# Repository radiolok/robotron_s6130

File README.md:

# Robotron S6130 и «Элема»: прошивки, схемы, документация

Реверс-инжиниринг и восстановление электронных пишущих машинок серии
**Robotron S6100** (ГДР, 1986–1989) и их советского аналога **«Элема» (ПЭЛК-3110)**.

| Машинка | Процессор | Статус | Документация |
|---|---|---|---|
| **Robotron S6130** | U880 (клон Z80), 2,46 МГц | ✅ **Работает.** Новая материнская плата, разблокирован RS-232 | [s6130/](s6130/README.md) |
| **«Элема» ПЭЛК-3110** | КР580ВМ80А (клон i8080) | 🛠 **Заготовка.** Прошивка снята, схема оцифрована, карта периферии сверена со схемой | [elema/](elema/README.md) |

История оживления «Роботрона»: статья на Хабре
[«Robotron S6130 — Восставший из мертвых»](https://habr.com/ru/companies/yadro/articles/886254/).

## Структура репозитория

```
s6130/            Robotron S6130
  README.md         обзор, журнал оживления, патчи, подключение к ПК
  fw/               дампы ПЗУ, листинг и база IDA, описание прошивки (README.md)
  hw/               описание железа (README.md), документация производителя (doc/),
                    схемы KiCad/DipTrace/draw.io (sch/), иллюстрации (img/)
elema/            «Элема» ПЭЛК-3110
  README.md         обзор и план оживления
  fw/               дампы ПЗУ, листинг i8080, описание прошивки (README.md)
  hw/               расшифровка схемы (README.md), склеенные листы, сканы (scans/),
                    таблицы разъёмов (netlist/)
tools/            общие скрипты
```

| Документ | Что внутри |
|---|---|
| [s6130/README.md](s6130/README.md) | Robotron S6130: обзор, опись файлов, журнал оживления, патчи прошивки, RS-232, инструментарий |
| [s6130/hw/README.md](s6130/hw/README.md) | S6130, железо: карта памяти, порты, прерывания, клавиатура, индикатор, двигатели, RS-232 и DIP-переключатели |
| [s6130/fw/README.md](s6130/fw/README.md) | S6130, **структура прошивки**: загрузка, главный цикл, прерывания, подсистемы, таблицы ПЗУ, переменные ОЗУ |
| [elema/README.md](elema/README.md) | «Элема»: обзор и план оживления |
| [elema/hw/README.md](elema/hw/README.md) | «Элема», железо: расшифровка принципиальной схемы (платы, микросхемы, разъёмы, дешифрация) |
| [elema/fw/README.md](elema/fw/README.md) | «Элема», **структура прошивки**: карта памяти и портов, прерывания ВН59, схема загрузки |

## Инструменты (`tools/`)

| Скрипт | Назначение |
|---|---|
| `z80_trace.py` | Превращает вывод Z80-декодера PulseView/sigrok в читаемую трассу (`.out`) и в Trace Events JSON для [Perfetto UI](https://ui.perfetto.dev) (флейм-чарт вызовов и обращений к портам) |
| `s6130_symbol.py` | Рисует таблицу символов из ПЗУ знакогенератора индикатора S6130 |
| `s6130_mem.py` | Описание карты памяти S6130 |
| `stitch_scans.py` | Склейка фрагментов скана одного листа (SIFT + аффинные преобразования; поворот и масштаб фрагментов любые). Нужен `opencv-python` |

```sh
# Трасса: export.txt — вывод декодера Z80 из PulseView, names.txt — экспорт имён функций из IDA
python3 tools/z80_trace.py -f export.txt -a names.txt              # S6130
python3 tools/z80_trace.py -f export.txt -a names.txt -m elema     # «Элема» (карта портов ПЭЛК)
# → export.txt.out (трасса) и export.txt.json (открыть в https://ui.perfetto.dev)

# Таблица символов индикатора
python3 tools/s6130_symbol.py -f s6130/fw/symbol_rom.bin -o charset.png

# Склейка листа схемы из фрагментов (--ref — номер фрагмента, задающего ориентацию)
python3 tools/stitch_scans.py -o sheet.png --ref 2 part1.jpg part2.jpg part3.jpg
```

Как устроен процесс отладки, описано в [s6130/README.md](s6130/README.md#инструментарий).

## Ссылки

- Статья: [Robotron S6130 — Восставший из мертвых](https://habr.com/ru/companies/yadro/articles/886254/) (Хабр, блог YADRO, 2025)
- [sigrok / PulseView](https://sigrok.org) — логический анализатор и декодер Z80
- [Perfetto UI](https://ui.perfetto.dev) — просмотр трасс

## Лицензия

[BSD 2-Clause](LICENSE). Документация производителя (`s6130/hw/doc/`, сканы в `elema/hw/`)
принадлежит правообладателям и приведена в справочных целях.

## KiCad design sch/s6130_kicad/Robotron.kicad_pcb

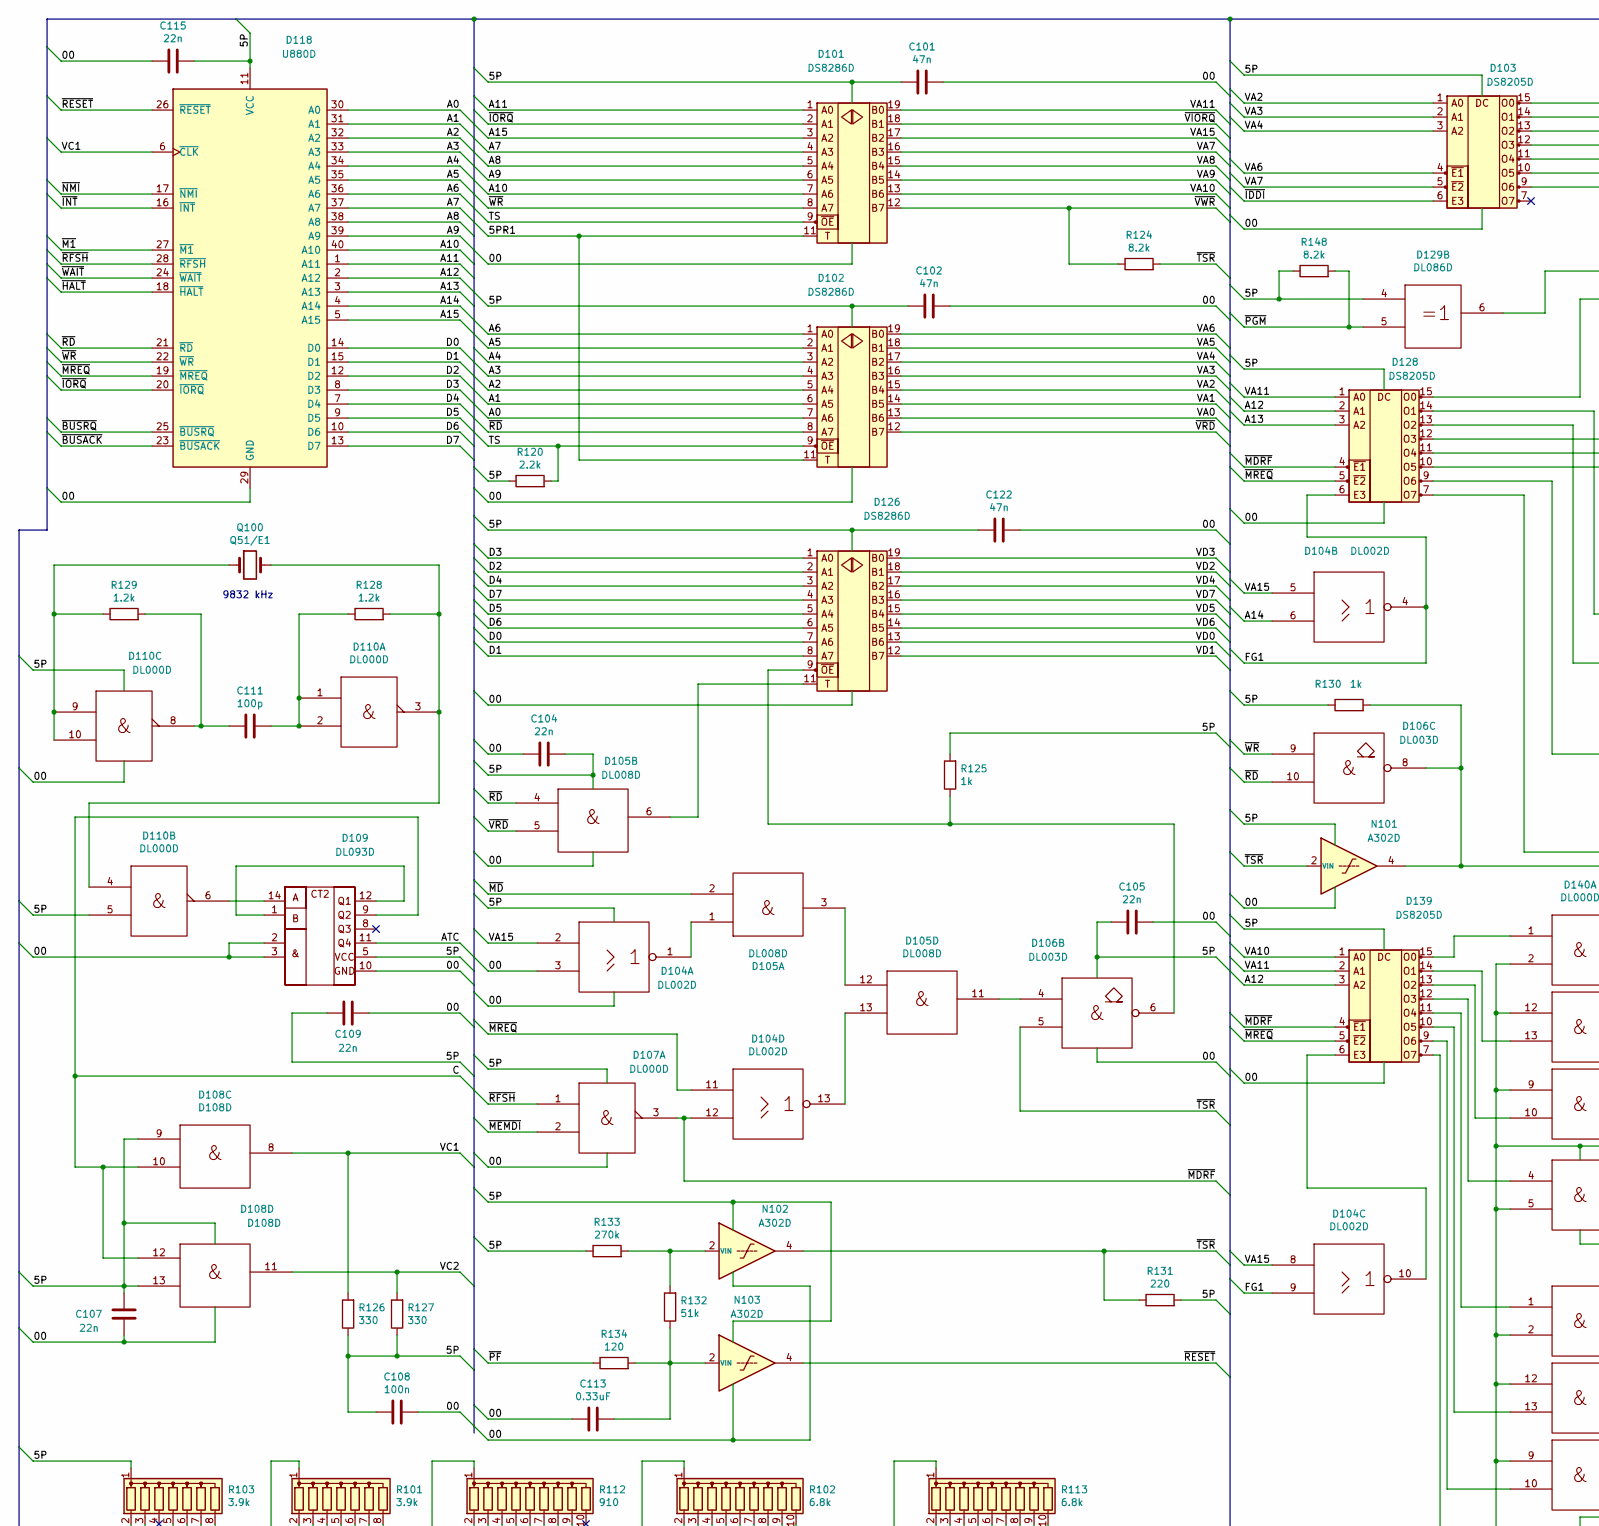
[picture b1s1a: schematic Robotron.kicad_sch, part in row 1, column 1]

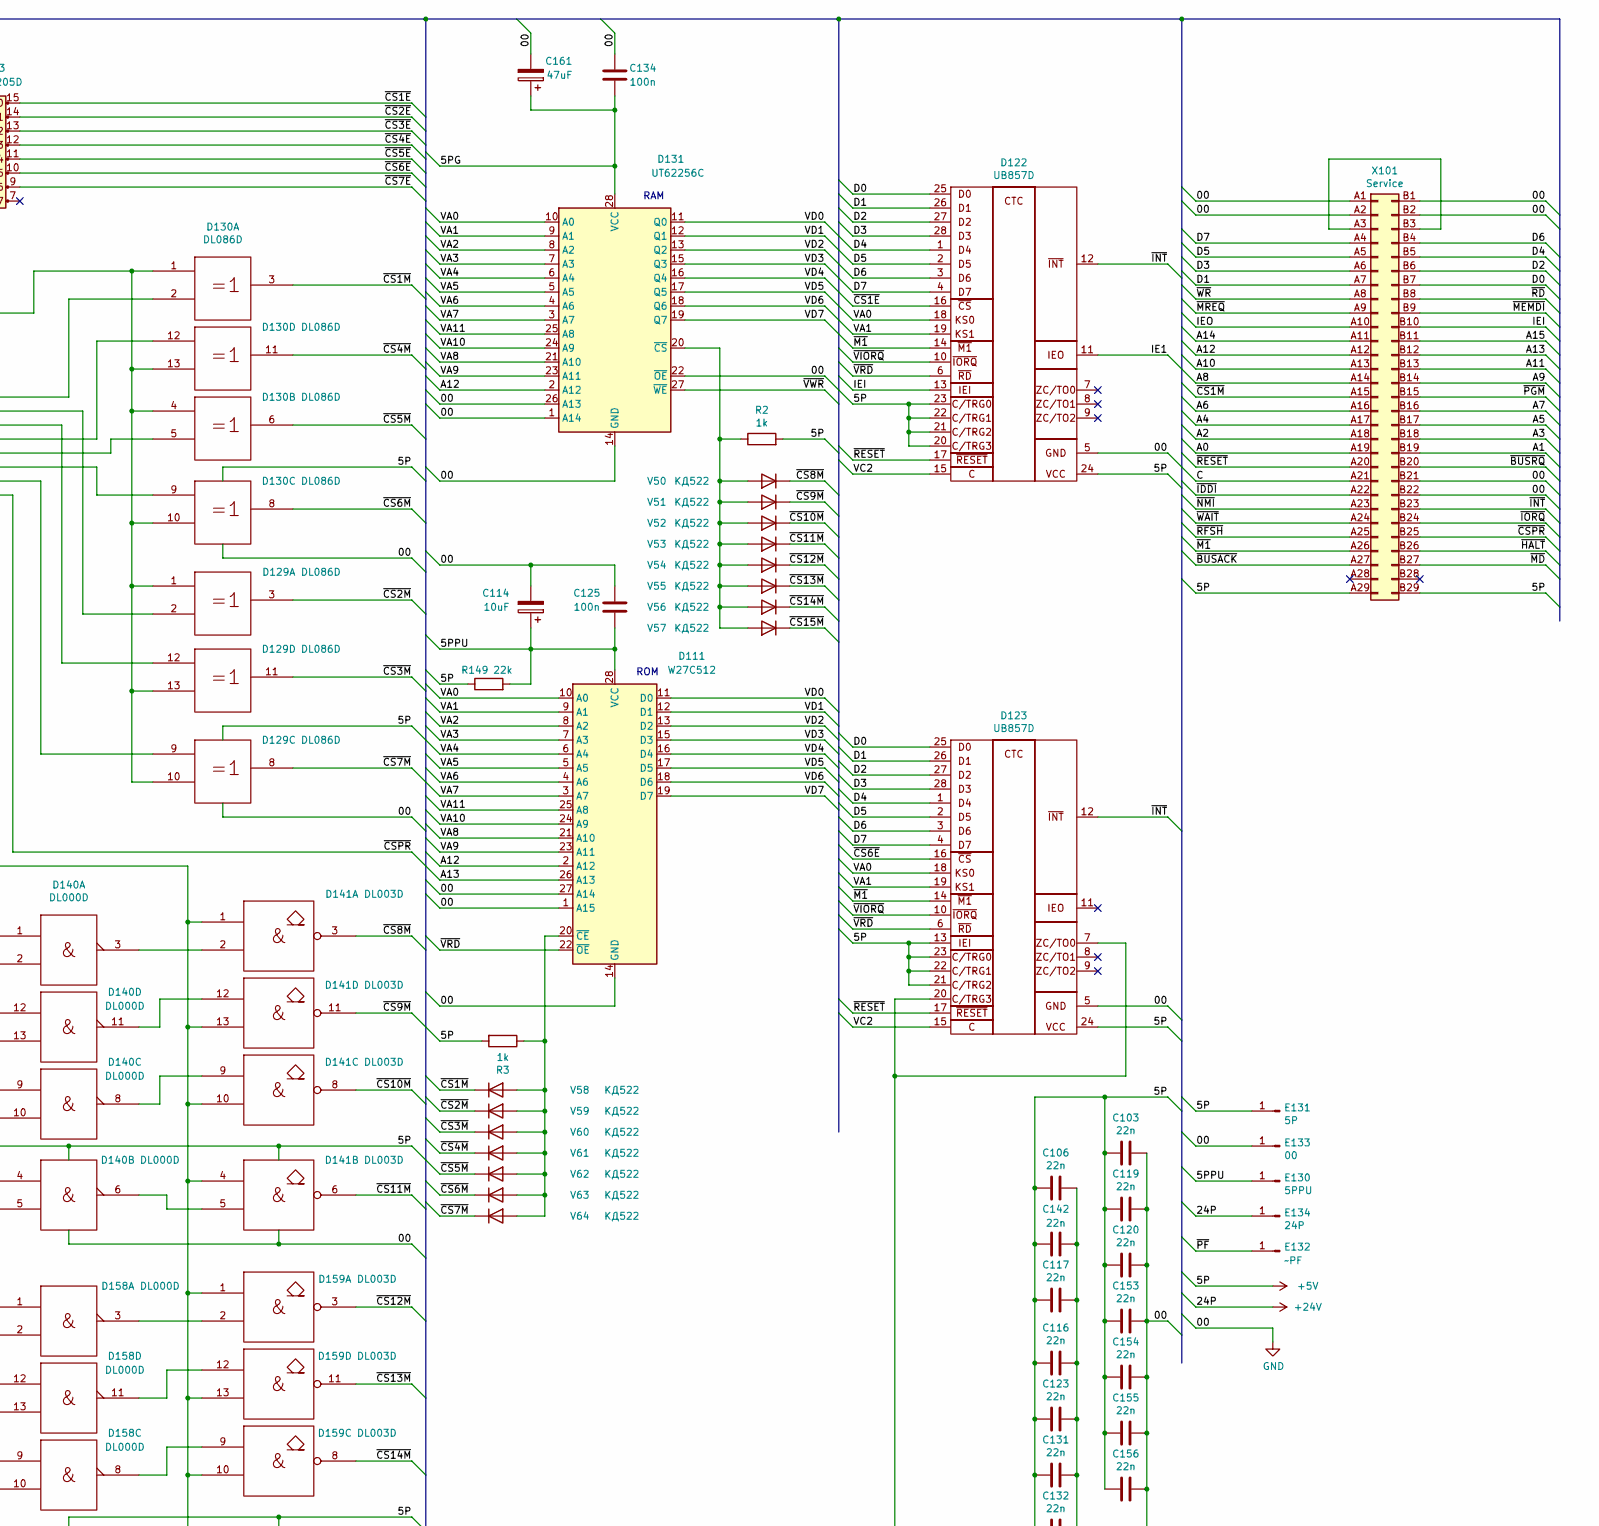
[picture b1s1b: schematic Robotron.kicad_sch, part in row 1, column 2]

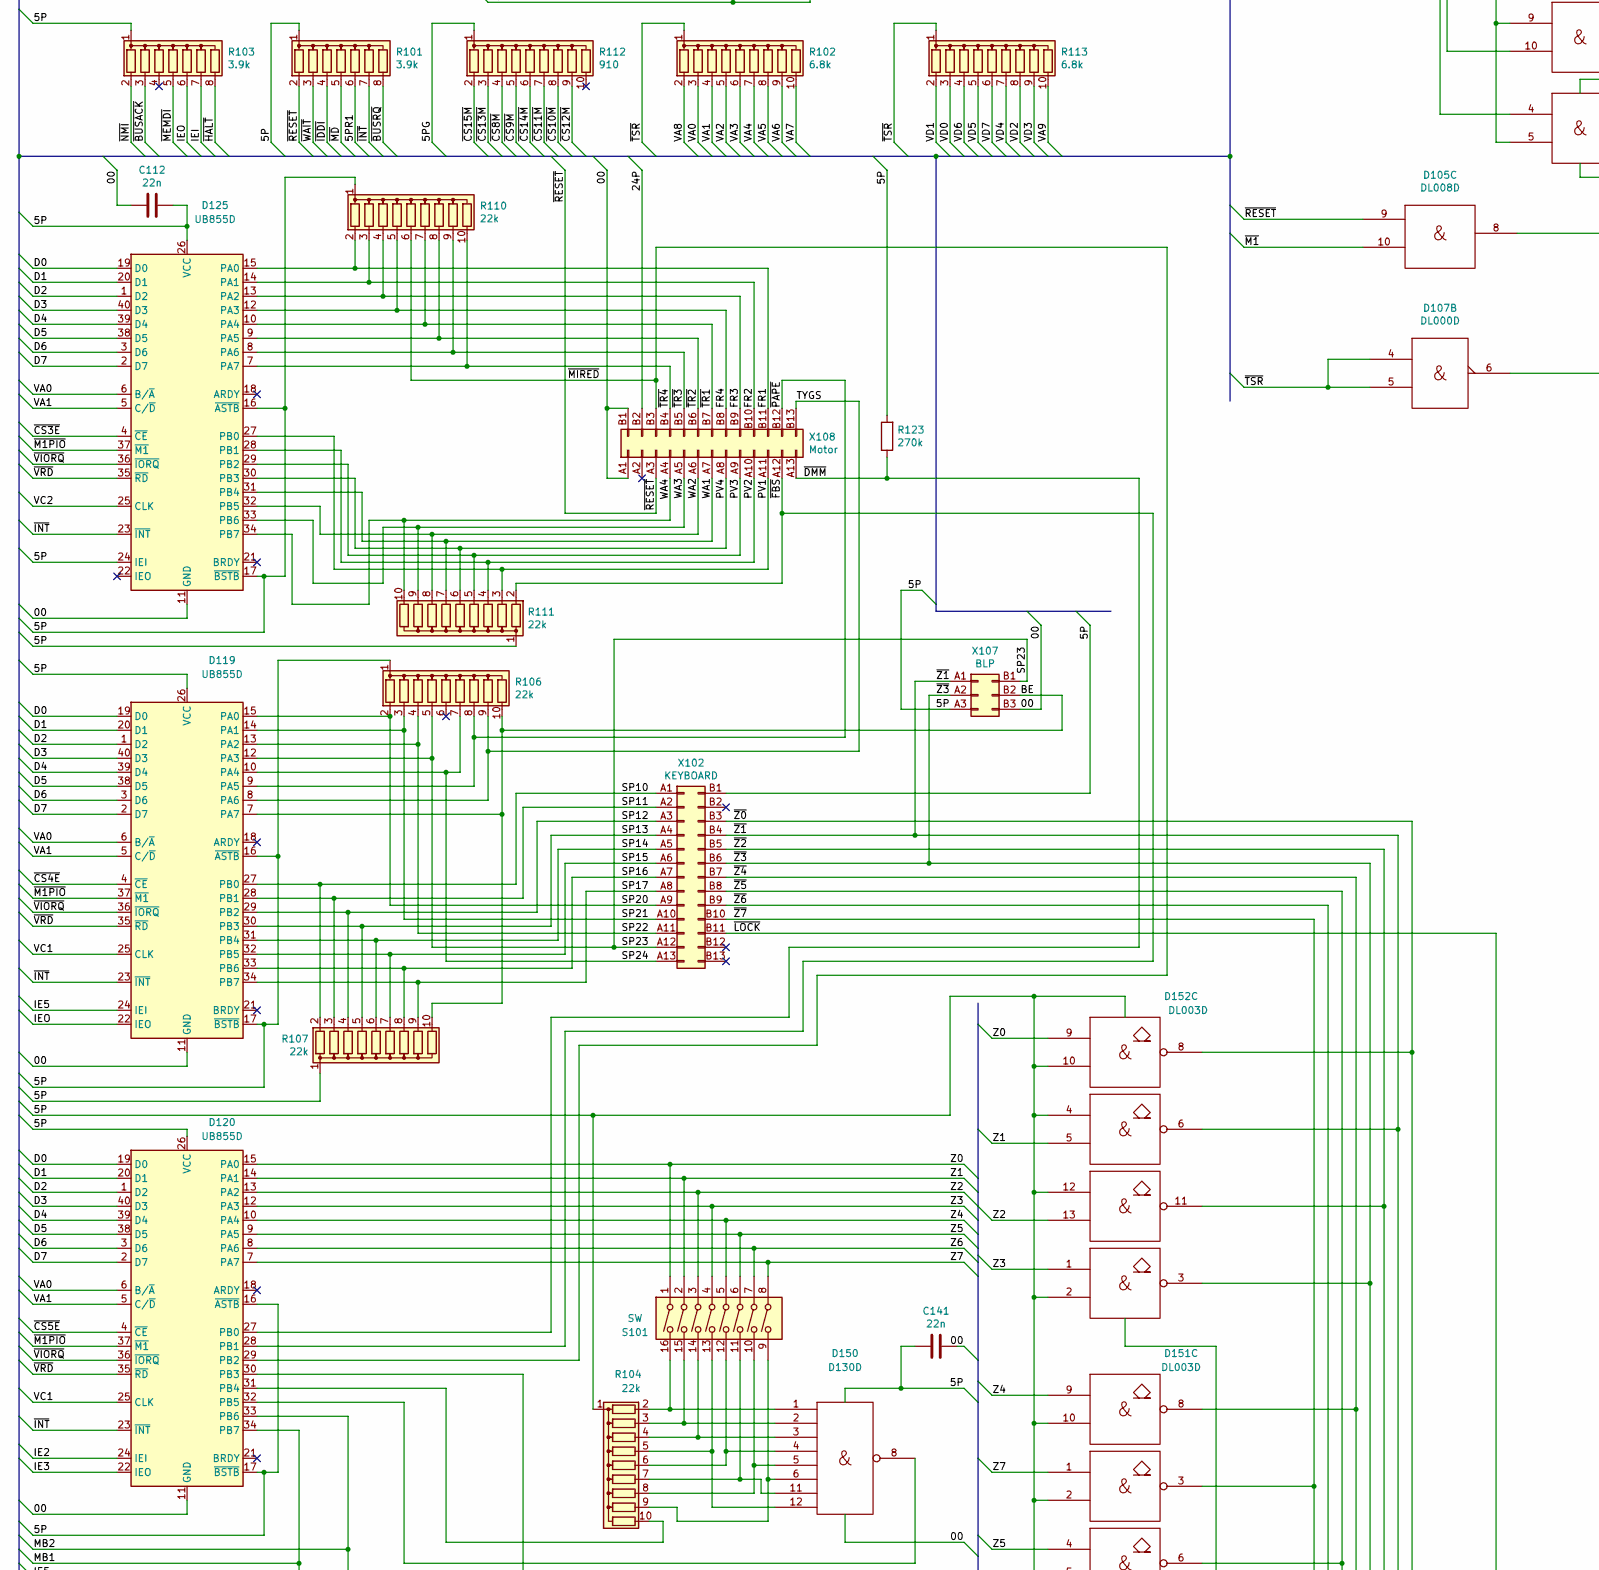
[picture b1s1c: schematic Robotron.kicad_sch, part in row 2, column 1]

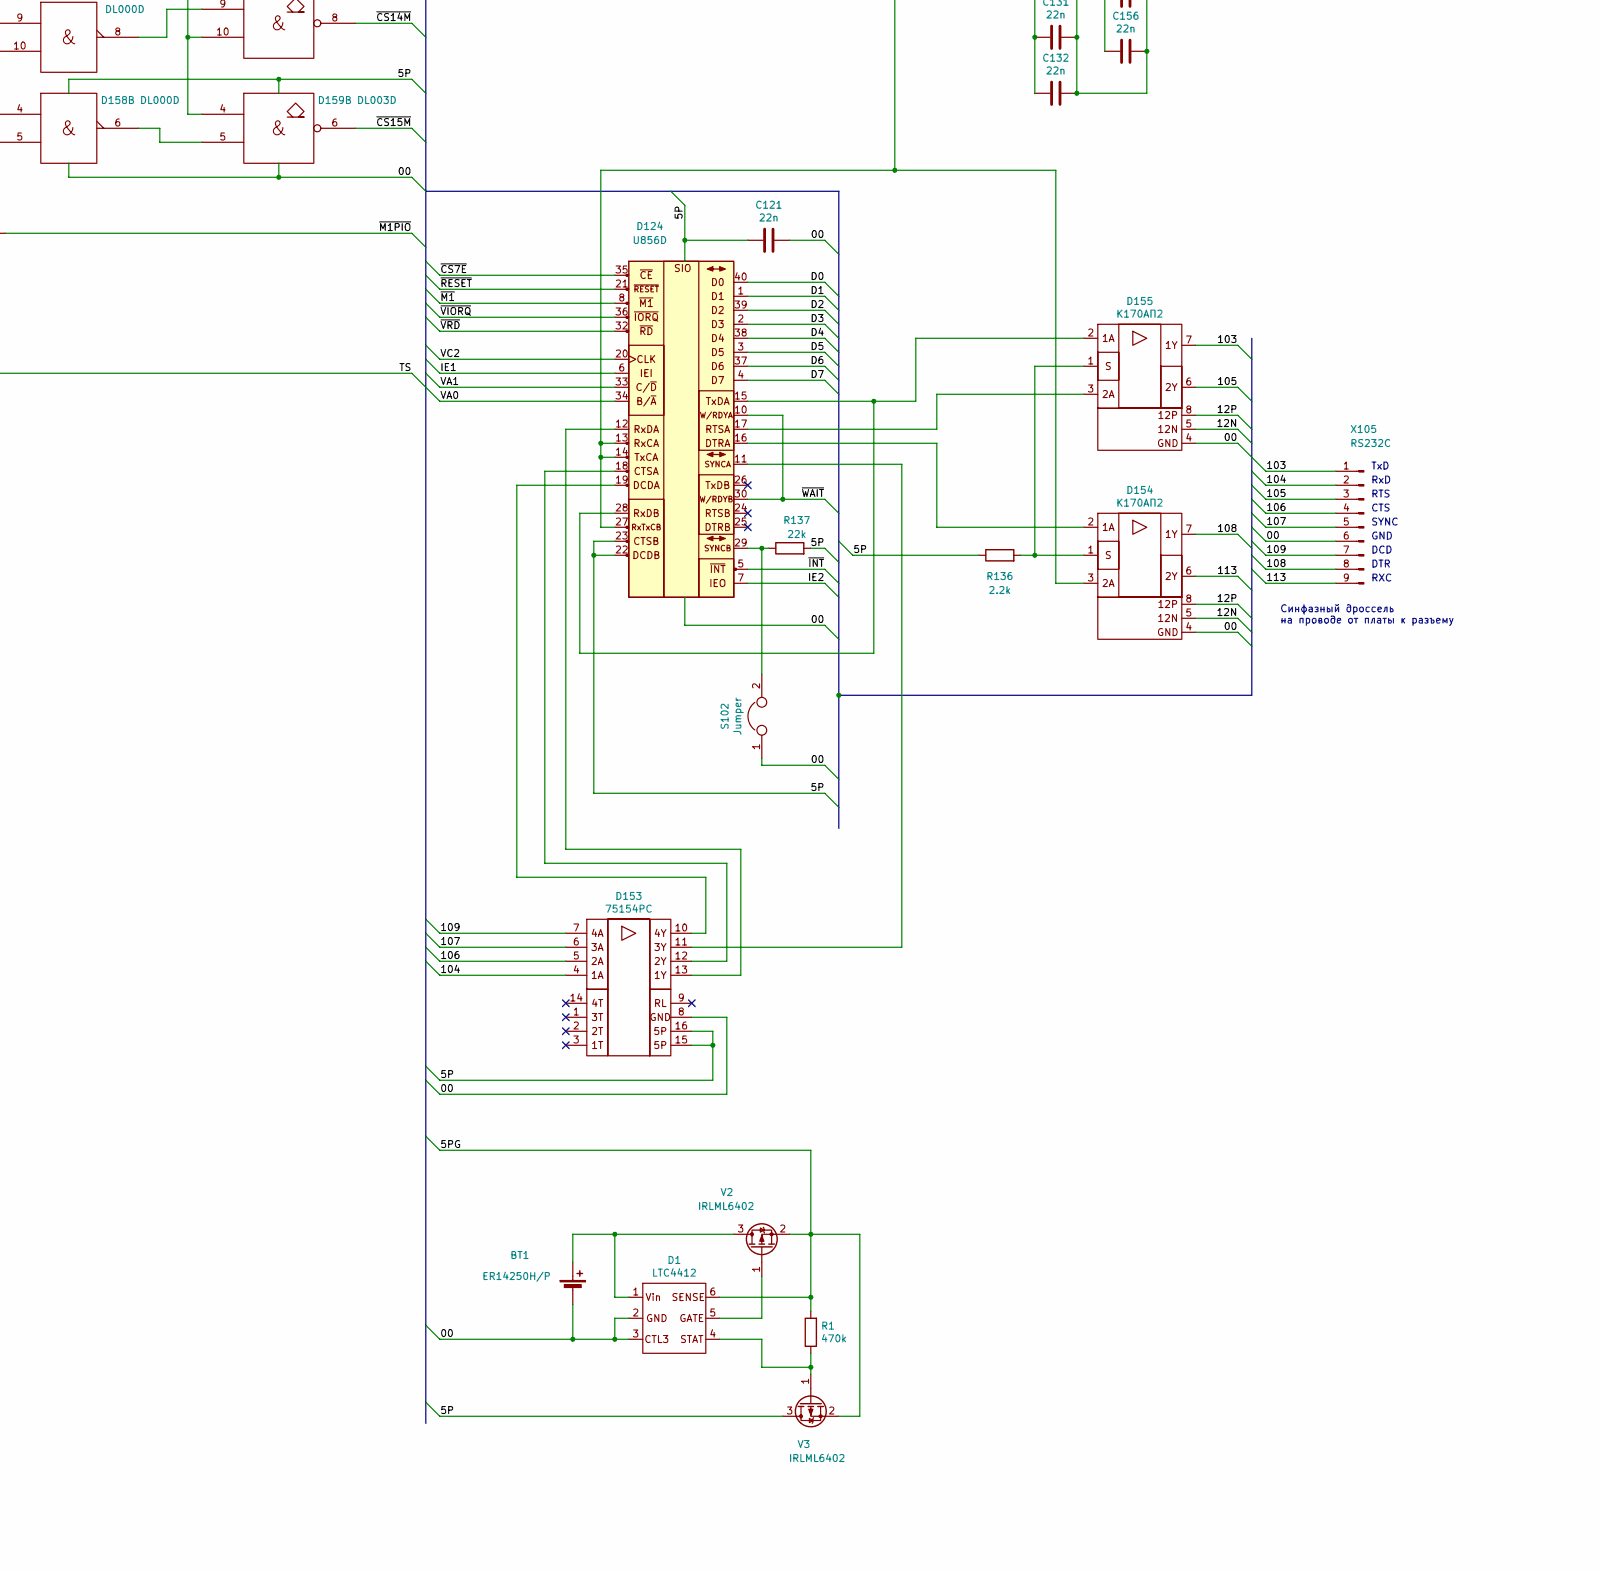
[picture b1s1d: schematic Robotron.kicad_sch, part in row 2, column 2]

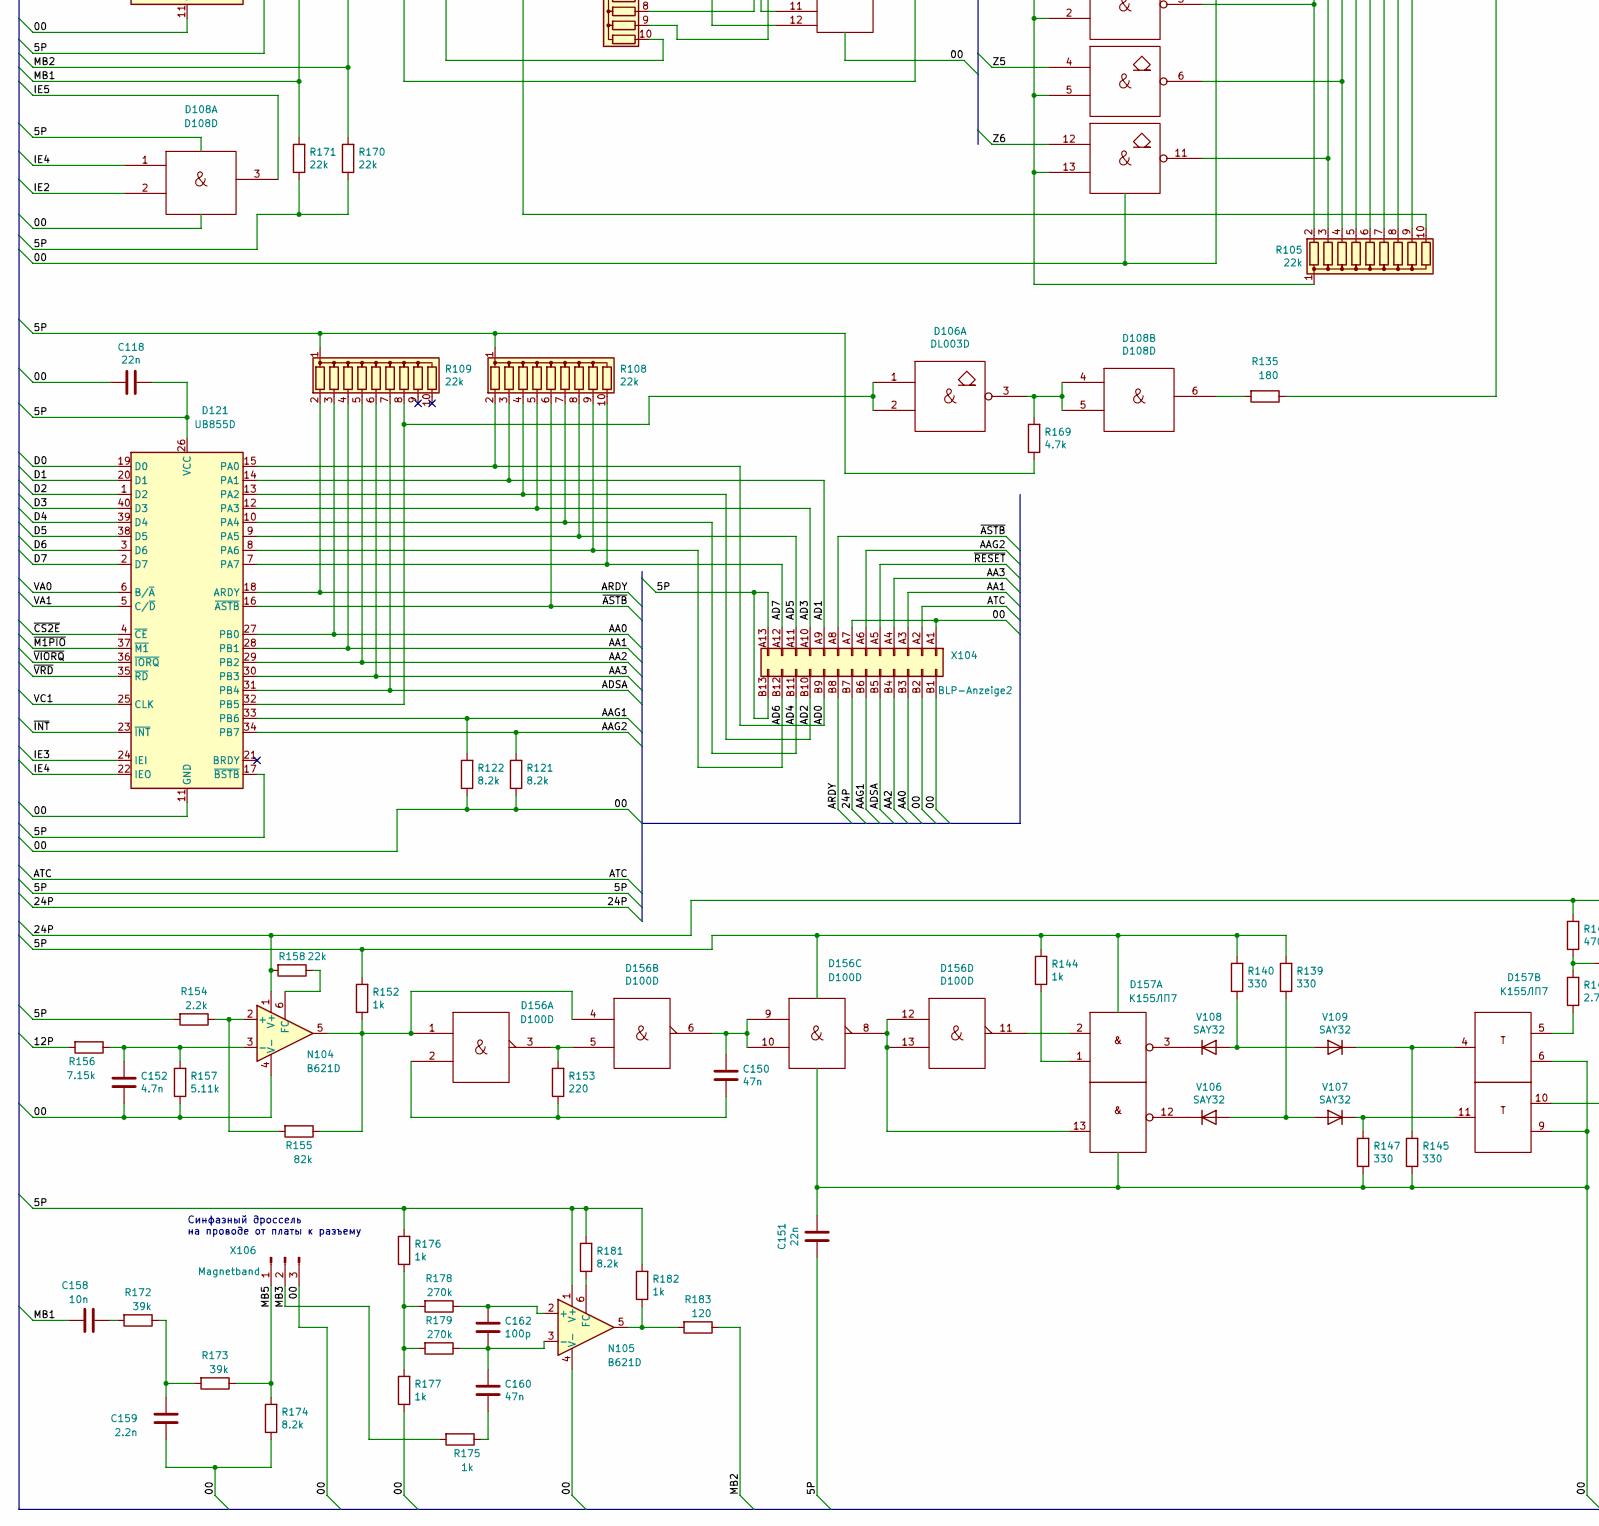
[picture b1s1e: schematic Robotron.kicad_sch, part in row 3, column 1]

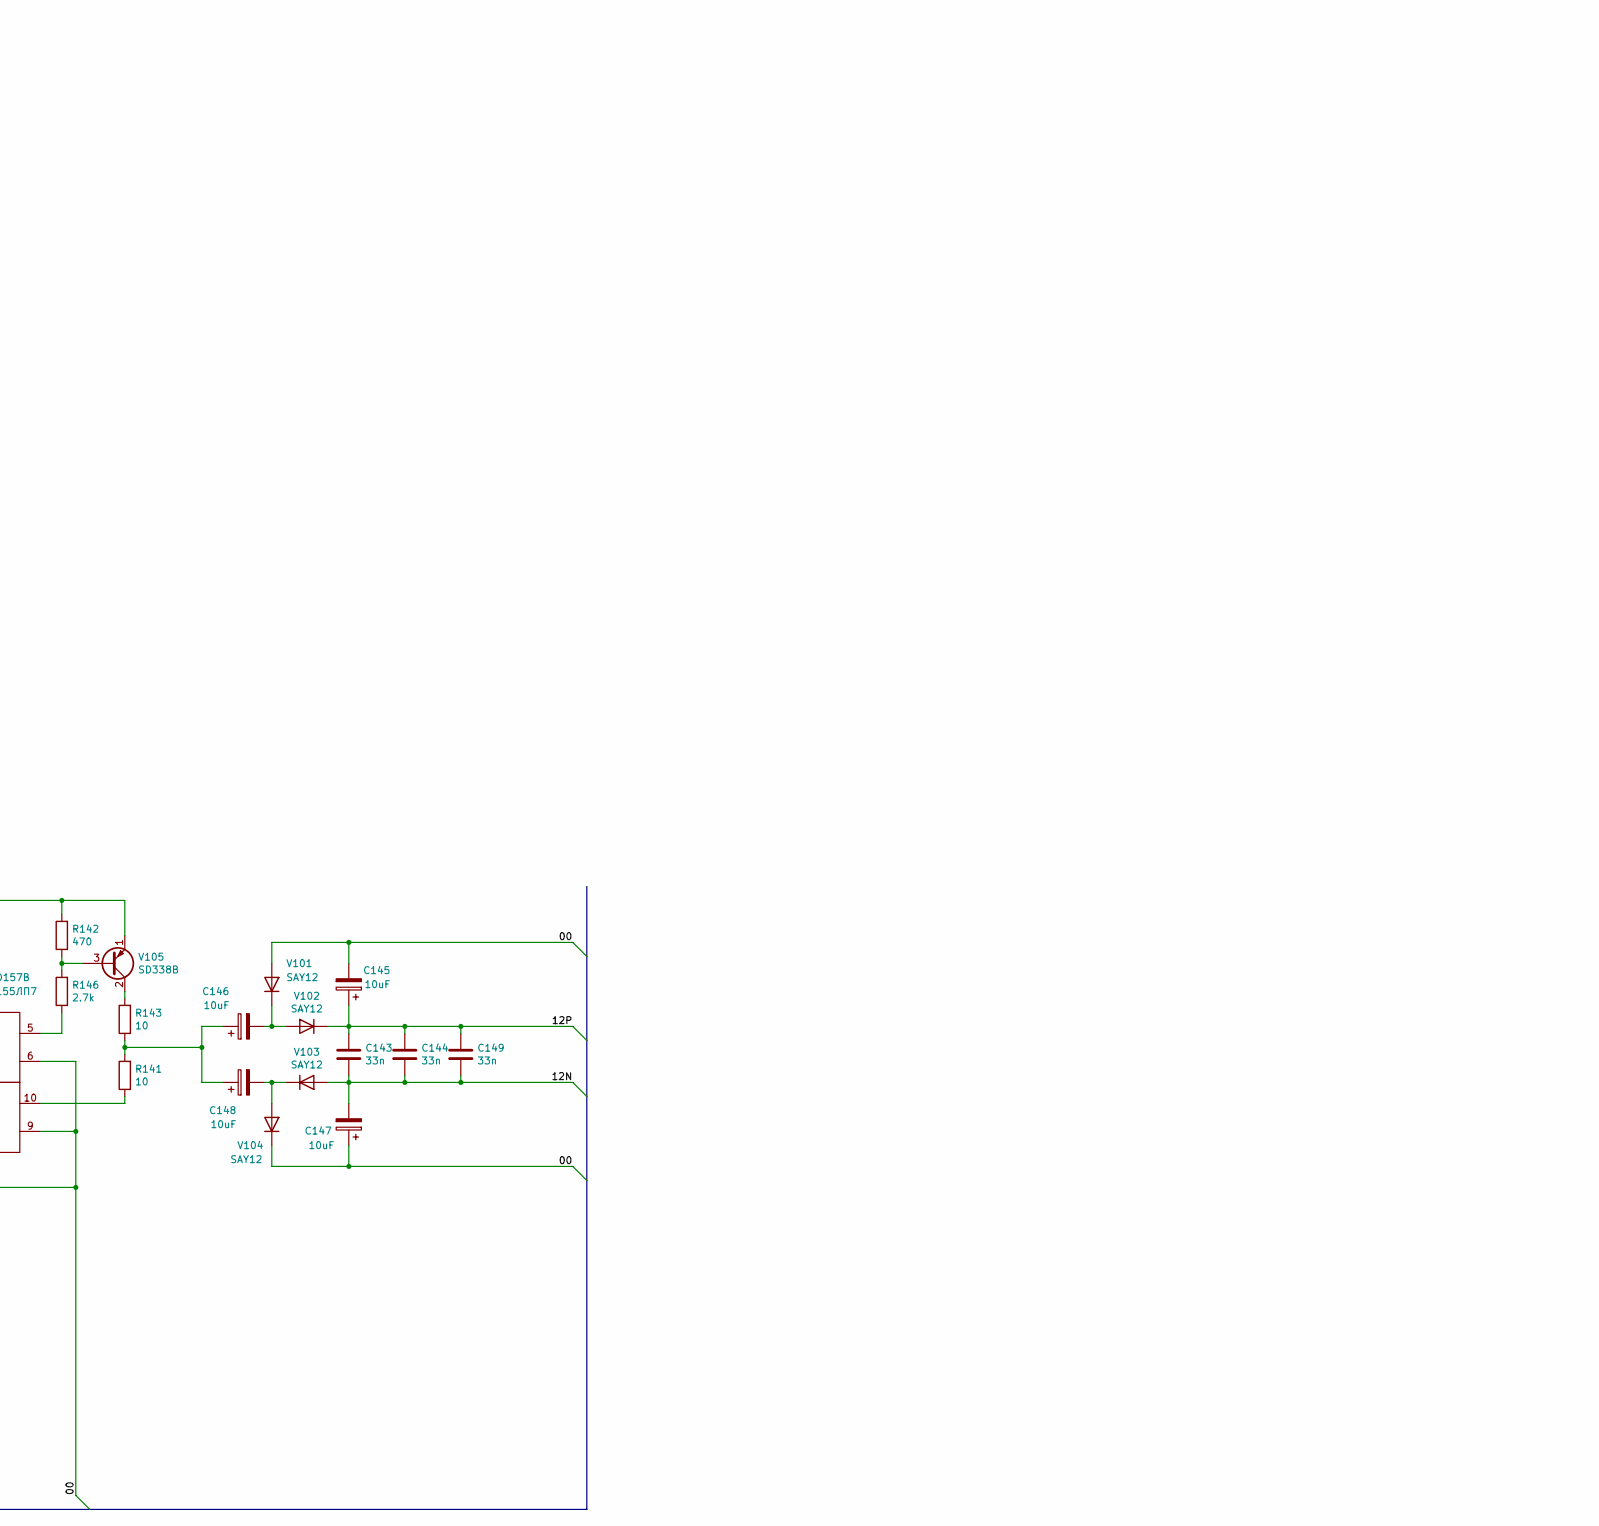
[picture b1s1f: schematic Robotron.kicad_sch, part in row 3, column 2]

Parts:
BT1: ER14250H/P; CP_Axial_L37.0mm_D16.0mm_P43.00mm_Horizontal
C101, C102, C122, C150, C160: 47n; C_Disc_D4.7mm_W2.5mm_P5.00mm
C103, C104, C105, C106, C107, C109, C112, C115, C116, C117, C118, C119, C120, C121, C123, C131, C132, C141, C142, C151, C153, C154, C155, C156: 22n; C_Disc_D4.7mm_W2.5mm_P5.00mm
C108, C125, C134: 100n; C_Disc_D4.7mm_W2.5mm_P5.00mm
C111, C162: 100p; C_Disc_D4.7mm_W2.5mm_P5.00mm
C113: 0.33uF; C_Axial_L17.0mm_D7.0mm_P25.00mm_Horizontal
C114, C145, C146, C147, C148: 10uF; CP_Radial_D5.0mm_P2.50mm
C143, C144, C149: 33n; C_Disc_D4.7mm_W2.5mm_P5.00mm
C152: 4.7n; C_Disc_D4.7mm_W2.5mm_P5.00mm
C158: 10n; C_Disc_D4.7mm_W2.5mm_P5.00mm
C159: 2.2n; C_Disc_D4.7mm_W2.5mm_P5.00mm
C161: 47uF; CP_Radial_D5.0mm_P2.50mm
D1: LTC4412; SOT-23-6
D101, D102, D126: DS8286D; DIP-20_W7.62mm_P2.5mm
D103, D128, D139: DS8205D; DIP-16_W7.62mm_P2.5
D104: DL002D; DIP-14_W7.62mm_2.5mm
D105: DL008D; DIP-14_W7.62mm_2.5mm
D106, D141, D151, D152, D159: DL003D; DIP-14_W7.62mm_2.5mm
D107, D110, D140, D158: DL000D; DIP-14_W7.62mm_2.5mm
D108: D108D; DIP-14_W7.62mm_2.5mm
D109: DL093D; DIP-14_W7.62mm_2.5mm
D111: W27C512; DIP-28_W15.24mm
D118: U880D; DIP-40_W15.24mm_P2.5
D119, D120, D121, D125: UB855D; DIP-40_W15.24mm_P2.5
D122, D123: UB857D; DIP-28_W15.24mm_P2.5mm
D124: U856D; DIP-40_W15.24mm_P2.5
D129, D130: DL086D; DIP-14_W7.62mm_2.5mm
D131: UT62256C; DIP-28_W15.24mm
D150: D130D; DIP-14_W7.62mm_2.5mm
D153: 75154PC; DIP-16_W7.62mm_P2.5
D154, D155: К170АП2; DIP-8_W7.62mm
D156: D100D; DIP-14_W7.62mm_2.5mm
D157: К155ЛП7; DIP-14_W7.62mm_2.5mm
E130: 5PPU; Pin_D1.3mm_L11.0mm
E131: 5P; Pin_D1.3mm_L11.0mm
E132: ~PF; Pin_D1.3mm_L11.0mm
E133: 00; Pin_D1.3mm_L11.0mm
E134: 24P; Pin_D1.3mm_L11.0mm
N101, N102, N103: A302D; DIP-4_W7.62mm
N104, N105: B621D; DIP-6_W7.62mm
Q100: Q51/E1; Crystal_HC49-U_Vertical
R1: 470k; R_0805_2012Metric_Pad1.15x1.40mm_HandSolder
R2, R3, R125, R130, R144, R152, R175, R176, R177, R182: 1k; R_Axial_DIN0207_L6.3mm_D2.5mm_P10.16mm_Horizontal
R101, R103: 3.9k; R_Array_SIP8
R102, R113: 6.8k; R_Array_SIP10
R104, R105, R106, R107, R108, R109, R110, R111: 22k; R_Array_SIP10
R112: 910; R_Array_SIP10
R120, R136, R154: 2.2k; R_Axial_DIN0207_L6.3mm_D2.5mm_P10.16mm_Horizontal
R121, R122, R124, R148, R174, R181: 8.2k; R_Axial_DIN0207_L6.3mm_D2.5mm_P10.16mm_Horizontal
R123, R133, R178, R179: 270k; R_Axial_DIN0207_L6.3mm_D2.5mm_P10.16mm_Horizontal
R126, R127, R139, R140, R145, R147: 330; R_Axial_DIN0207_L6.3mm_D2.5mm_P10.16mm_Horizontal
R128, R129: 1.2k; R_Axial_DIN0207_L6.3mm_D2.5mm_P10.16mm_Horizontal
R131, R153: 220; R_Axial_DIN0207_L6.3mm_D2.5mm_P10.16mm_Horizontal
R132: 51k; R_Axial_DIN0207_L6.3mm_D2.5mm_P10.16mm_Horizontal
R134, R183: 120; R_Axial_DIN0207_L6.3mm_D2.5mm_P10.16mm_Horizontal
R135: 180; R_Axial_DIN0207_L6.3mm_D2.5mm_P10.16mm_Horizontal
R137, R149, R158, R170, R171: 22k; R_Axial_DIN0207_L6.3mm_D2.5mm_P10.16mm_Horizontal
R141, R143: 10; R_Axial_DIN0207_L6.3mm_D2.5mm_P10.16mm_Horizontal
R142: 470; R_Axial_DIN0207_L6.3mm_D2.5mm_P10.16mm_Horizontal
R146: 2.7k; R_Axial_DIN0207_L6.3mm_D2.5mm_P10.16mm_Horizontal
R155: 82k; R_Axial_DIN0207_L6.3mm_D2.5mm_P10.16mm_Horizontal
R156: 7.15k; R_Axial_DIN0207_L6.3mm_D2.5mm_P10.16mm_Horizontal
R157: 5.11k; R_Axial_DIN0207_L6.3mm_D2.5mm_P10.16mm_Horizontal
R169: 4.7k; R_Axial_DIN0207_L6.3mm_D2.5mm_P10.16mm_Horizontal
R172, R173: 39k; R_Axial_DIN0207_L6.3mm_D2.5mm_P10.16mm_Horizontal
S101: SW; SW_DIP_SPSTx08_Slide_9.78x22.5mm_W7.62mm_P2.54mm
S102: Jumper; PinHeader_2x01_P2.54mm_Vertical
V2, V3: IRLML6402; SOT-23
V50, V51, V52, V53, V54, V55, V56, V57, V58, V59, V60, V61, V62, V63, V64: КД522; D_DO-35_SOD27_P10.16mm_Horizontal
V101, V102, V103, V104: SAY12; TO-92S-2
V105: SD338B; TO-126-3_Vertical
V106, V107, V108, V109: SAY32; TO-92S-2
X101: Service; Service_connector
X102: KEYBOARD; 2X13_PIN_CONNECTOR
X104: BLP-Anzeige2; 2X13_PIN_CONNECTOR
X105: RS232C; PinHeader_1x09_P2.54mm_Vertical
X106: Magnetband; FanPinHeader_1x03_P2.54mm_Vertical
X107: BLP; 2X3_PIN_CONNECTOR
X108: Motor; 2X13_PIN_CONNECTOR

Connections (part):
+5V: C101.1, C102.1, C103.1, C104.2, C105.1, C106.1, C107.2, C108.1, C109.1, C112.2, C115.2, C116.1, C117.1, C118.2, C119.1, C120.1, C121.1, C122.1, C123.1, C131.1, C132.1, C141.1, C142.1, C151.1, C153.1, C154.1, C155.1, C156.1, D101.20 (VCC), D102.20 (VCC), D103.16 (VCC), D104.14 (VCC), D105.14 (Vcc), D106.14 (Vcc), D107.14 (Vcc), D108.9, D108.13, D108.14 (Vcc), D109.5, D110.5, D110.14 (Vcc), D118.11 (VCC), D119.16 (~ASTB), D119.17 (~BSTB), D119.26 (VCC), D120.16 (~ASTB), D120.17 (~BSTB), D120.26 (VCC), D121.17 (~BSTB), D121.26 (VCC), D122.20, D122.21, D122.22, D122.23, D122.24, D123.13, D123.21, D123.22, D123.23, D123.24, D124.9 (VCC), D124.22 (DCDB), D124.23 (CTSB), D125.16 (~ASTB), D125.17 (~BSTB), D125.24 (IEI), D125.26 (VCC), D126.20 (VCC), D128.16 (VCC), D129.4, D129.14 (Vcc), D130.14 (Vcc), D139.16 (VCC), D140.2, D140.5, D140.9, D140.12, D140.14 (Vcc), D141.14 (Vcc), D150.14 (Vcc), D151.2, D151.5, D151.10, D151.13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; also elsewhere on the board
+24V: E134.1, N104.1 (V+), R142.2, R158.2, V105.1 (E), X104.B7, X108.B2
/5PG: C134.1, C161.1, D1.6, D131.28 (VCC), R1.2, R112.1 (common), V2.2 (S), V3.2 (S); also elsewhere on the board
/5PPU: C114.1, C125.1, D111.28 (VCC), E130.1, R149.2
/5PR1: D101.11 (STB), D102.11 (STB), R101.6 (R5)
/12N: C143.2, C144.2, C147.2, C149.2, D154.5, D155.5, V103.2 (A)
/12P: C143.1, C144.1, C145.1, C149.1, D154.8, D155.8, R156.2, V102.1 (K)
/103: D155.7, X105.1
/104: D153.4, X105.2
/105: D155.6, X105.3
/106: D153.5, X105.4
/107: D153.6, X105.5
/108: D154.7, X105.8
/109: D153.7, X105.7
/113: D154.6, X105.9
/A0: D102.7 (A7), D118.30 (A0), X101.A19
/A1: D102.6 (A6), D118.31 (A1), X101.B19
/A2: D102.5 (A5), D118.32 (A2), X101.A18
/A3: D102.4 (A4), D118.33 (A3), X101.B18
/A4: D102.3 (A3), D118.34 (A4), X101.A17
/A5: D102.2 (A2), D118.35 (A5), X101.B17
/A6: D102.1 (A1), D118.36 (A6), X101.A16
/A7: D101.4 (A4), D118.37 (A7), X101.B16
/A8: D101.5 (A5), D118.38 (A8), X101.A14
/A9: D101.6 (A6), D118.39 (A9), X101.B14
/A10: D101.7 (A7), D118.40 (A10), X101.A13
/A11: D101.1 (A1), D118.1 (A11), X101.B13
/A12: D111.2 (A12), D118.2 (A12), D128.2 (B), D131.2 (A12), D139.3 (C), X101.A12
/A13: D111.26 (A13), D118.3 (A13), D128.3 (C), X101.B12
/A14: D104.6, D118.4 (A14), X101.A11
/A15: D101.3 (A3), D118.5 (A15), X101.B11
/AA0: D121.27 (PB0), R109.3 (R2), X104.B3
/AA1: D121.28 (PB1), R109.4 (R3), X104.A3
/AA2: D121.29 (PB2), R109.5 (R4), X104.B4
/AA3: D121.30 (PB3), R109.6 (R5), X104.A4
/AAG1: D121.33 (PB6), R122.2, X104.B6
/AAG2: D121.34 (PB7), R121.2, X104.A6
/AD0: D121.15 (PA0), R108.2 (R1), X104.B9
/AD1: D121.14 (PA1), R108.3 (R2), X104.A9
/AD2: D121.13 (PA2), R108.4 (R3), X104.B10
/AD3: D121.12 (PA3), R108.5 (R4), X104.A10
/AD4: D121.10 (PA4), R108.7 (R6), X104.B11
/AD5: D121.9 (PA5), R108.8 (R7), X104.A11
/AD6: D121.8 (PA6), R108.9 (R8), X104.B12
/AD7: D121.7 (PA7), R108.10 (R9), X104.A12
/ADSA: D121.31 (PB4), R109.7 (R6), X104.B5
/ARDY: D121.18 (ARDY), R109.2 (R1), X104.B8
/ATC: D109.11, X104.A2
/BE: D119.7 (PA7), R106.10 (R9), R107.10 (R9), X107.B2
/C: D108.10, D108.12, D109.9, X101.A21
/D0: D118.14 (D0), D119.19 (D0), D120.19 (D0), D121.19 (D0), D122.25, D123.25, D124.40 (D0), D125.19 (D0), D126.7 (A7), X101.B7
/D1: D118.15 (D1), D119.20 (D1), D120.20 (D1), D121.20 (D1), D122.26, D123.26, D124.1 (D1), D125.20 (D1), D126.8 (A8), X101.A7
/D2: D118.12 (D2), D119.1 (D2), D120.1 (D2), D121.1 (D2), D122.27, D123.27, D124.39 (D2), D125.1 (D2), D126.2 (A2), X101.B6
/D3: D118.8 (D3), D119.40 (D3), D120.40 (D3), D121.40 (D3), D122.28, D123.28, D124.2 (D3), D125.40 (D3), D126.1 (A1), X101.A6
/D4: D118.7 (D4), D119.39 (D4), D120.39 (D4), D121.39 (D4), D122.1, D123.1, D124.38 (D4), D125.39 (D4), D126.3 (A3), X101.B5
/D5: D118.9 (D5), D119.38 (D5), D120.38 (D5), D121.38 (D5), D122.2, D123.2, D124.3 (D5), D125.38 (D5), D126.5 (A5), X101.A5
/D6: D118.10 (D6), D119.3 (D6), D120.3 (D6), D121.3 (D6), D122.3, D123.3, D124.37 (D6), D125.3 (D6), D126.6 (A6), X101.B4
/D7: D118.13 (D7), D119.2 (D7), D120.2 (D7), D121.2 (D7), D122.4, D123.4, D124.4 (D7), D125.2 (D7), D126.4 (A4), X101.A4
/FG1: D104.4, D104.9, D128.6 (E3)
/FR1: D125.15 (PA0), R110.2 (R1), X108.B11
/FR2: D125.14 (PA1), R110.3 (R2), X108.B10
/FR3: D125.13 (PA2), R110.4 (R3), X108.B9
/FR4: D125.12 (PA3), R110.5 (R4), X108.B8
/IE1: D122.11, D124.6 (IEI)
/IE2: D108.2, D120.24 (IEI), D124.7 (IEO)
/IE3: D120.22 (IEO), D121.24 (IEI)
/IE4: D108.1, D121.22 (IEO)
/IE5: D108.3, D119.24 (IEI)
/IEI: D122.13, R103.7 (R6), X101.B10
/IEO: D119.22 (IEO), R103.6 (R5), X101.A10
/MB1: C158.1, D120.34 (PB7), R171.2
/MB2: D120.33 (PB6), R170.2, R183.1
/MB3: R175.2, X106.2
/MB5: R173.1, R174.2, X106.1
/PV1: D125.27 (PB0), R111.3 (R2), X108.A11
/PV2: D125.28 (PB1), R111.4 (R3), X108.A10
/PV3: D125.29 (PB2), R111.5 (R4), X108.A9
/PV4: D125.30 (PB3), R111.6 (R5), X108.A8
/SP10: D119.27 (PB0), R107.2 (R1), X102.A1
/SP11: D119.28 (PB1), R107.3 (R2), X102.A2
/SP12: D119.29 (PB2), R107.4 (R3), X102.A3
/SP13: D119.30 (PB3), R107.5 (R4), X102.A4
/SP14: D119.31 (PB4), R107.6 (R5), X102.A5
/SP15: D119.32 (PB5), R107.7 (R6), X102.A6
/SP16: D119.33 (PB6), R107.8 (R7), X102.A7
/SP17: D119.34 (PB7), R107.9 (R8), X102.A8
/SP20: D119.15 (PA0), R106.2 (R1), X102.A9
/SP21: D119.14 (PA1), R106.3 (R2), X102.A10
/SP22: D119.13 (PA2), R106.4 (R3), X102.A11
/SP23: D119.12 (PA3), R106.5 (R4), X102.A12, X107.B1
/SP24: D119.10 (PA4), R106.7 (R6), X102.A13
/TS: D101.9 (~OE), D102.9 (~OE), D107.6, R120.2
/TYGS: D119.8 (PA6), R106.9 (R8), X108.B13
/VA0: D102.13 (Y7), D111.10 (A0), D119.6 (B/~A), D120.6 (B/~A), D121.6 (B/~A), D122.18, D123.18, D124.34 (B/~A), D125.6 (B/~A), D131.10 (A0), R102.3 (R2)
/VA1: D102.14 (Y6), D111.9 (A1), D119.5 (C/~D), D120.5 (C/~D), D121.5 (C/~D), D122.19, D123.19, D124.33 (C/~D), D125.5 (C/~D), D131.9 (A1), R102.4 (R3)
/VA2: D102.15 (Y5), D103.1 (A), D111.8 (A2), D131.8 (A2), R102.5 (R4)
/VA3: D102.16 (A4), D103.2 (B), D111.7 (A3), D131.7 (A3), R102.6 (R5)
/VA4: D102.17 (Y3), D103.3 (C), D111.6 (A4), D131.6 (A4), R102.7 (R6)
/VA5: D102.18 (Y2), D111.5 (A5), D131.5 (A5), R102.8 (R7)
/VA6: D102.19 (Y1), D103.4 (~E1), D111.4 (A6), D131.4 (A6), R102.9 (R8)
/VA7: D101.16 (A4), D103.5 (~E2), D111.3 (A7), D131.3 (A7), R102.10 (R9)
/VA8: D101.15 (Y5), D111.21 (A10), D131.21 (A10), R102.2 (R1)
/VA9: D101.14 (Y6), D111.23 (A11), D131.23 (A11), R113.10 (R9)
/VA10: D101.13 (Y7), D111.24 (A9), D131.24 (A9), D139.1 (A)
/VA11: D101.19 (Y1), D111.25 (A8), D128.1 (A), D131.25 (A8), D139.2 (B)
/VA15: D101.17 (Y3), D104.2, D104.5, D104.8
/VC1: D108.8, D118.6 (~CLK), D119.25 (CLK), D120.25 (CLK), D121.25 (CLK), R126.2
/VC2: D108.11, D122.15, D123.15, D124.20 (CLK), D125.25 (CLK), R127.2
/VD0: D111.11 (D0), D126.13 (Y7), D131.11 (Q0), R113.3 (R2)
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
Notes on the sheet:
SYNC
RxD
RTS
RAM
CTS
Синфазный дроссель на проводе от платы к разъему
GND
TxD
ROM
9832 kHz
DCD
RXC
DTR

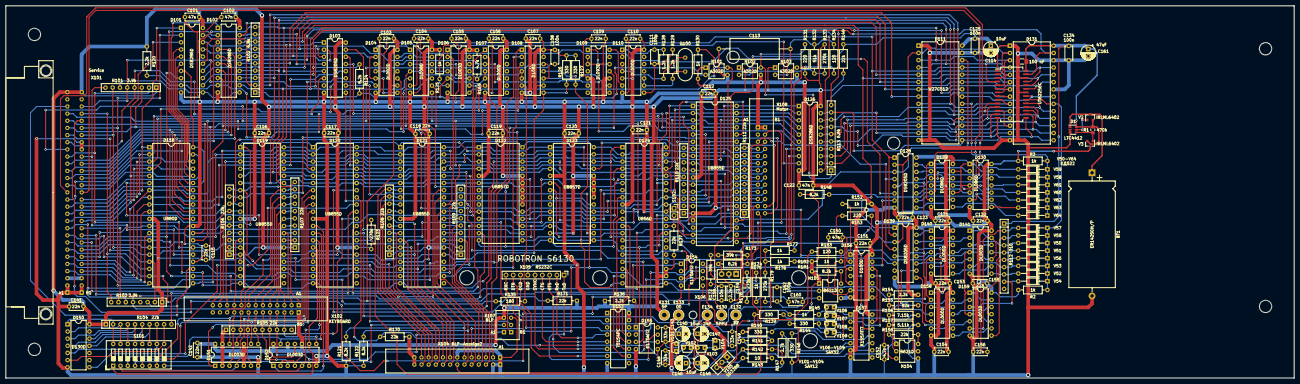
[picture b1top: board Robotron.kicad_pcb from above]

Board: 2 copper layers, 450.0 x 130.0 mm, 200 parts (0 on the bottom side), 295 nets.

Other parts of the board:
100 nF: C_1206; C_1206_3216Metric_Pad1.42x1.75mm_HandSolder
C110: 22n; C_Disc_D4.7mm_W2.5mm_P5.00mm

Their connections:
+5V: C110.2; also elsewhere on the board
/5PG: 100 nF.2; also elsewhere on the board
GND: 100 nF.1, C110.1; also elsewhere on the board

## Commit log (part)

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2019-09-20 Add documentation
2019-09-21 Start redraw the schema
2019-10-10 More digitized schema
2019-10-10 Add S6130 and PELK binaries
2019-10-10 Add assemblies
2019-10-10 S6130 Modules map
2019-10-11 Use DZ80 disassembly
2020-06-25 Add bin files
2020-06-25 schematic update
2020-06-25 modified files
2025-02-10 add ida pro and some scripts
2025-02-18 Update z80.py
    pylint checks
2025-02-18 update ida files
2025-02-18 Update Z80 script
2025-02-18 fix proper symbol_rom
2025-02-18 Enable Uart handlers
2025-02-25 feat: modified ROM with RS-232 Enabled
2025-02-25 add docs
2025-02-27 update ida and sch
2025-02-27 add s6130 pcb files
2025-02-27 add RS-232 info
